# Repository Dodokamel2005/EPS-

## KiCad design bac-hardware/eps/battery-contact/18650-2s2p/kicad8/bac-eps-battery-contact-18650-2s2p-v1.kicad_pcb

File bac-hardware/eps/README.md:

# EPS v1
## Requirements
[comment]: <> (TODO turn reqs into specs on first release)
v1 of the EPS takes a low-effort approach to facilitate achieving an MVP for the whole system before starting to optimise individual subsystems. Given requirements for all parts are:

- Wide operating temperature range (industrial or automotive grade)
- Easy implementation (low BOM, good EMI/SI characteristics, solid documentation)
- Predictable availability
- Reasonable cost
- As few plastic parts as possible (low outgassing)

### PMIC
#### Minimal Requirements
- [x] Usable for both USB and solar charging
- [x] MPPT
- [x] 2S Li-Ion battery charging
- [x] Enable input pin
- [x] Fault output pin
- [x] Full complement of safety features: OVP, OCP, OTP, RVP, BBD

#### Optional Requirements
- [x] Fault output pin
- [x] Support for 1s to 4s battery packs
- [x] Support for LiFePo4 batteries
- [ ] I2C telemetry
- [ ] Adjustable charging current
- [ ] Cell balancing for 2s and 4s battery packs

### DC Buck Converter
#### Minimal Requirements
- [x] Input voltage range: 6 V to 9 V
- [x] Output voltage range: 3.3 to 5 V
- [x] 3 A per output
- [x] Enable pin
- [x] Fault output pin
- [x] Full complement of safety features: OCP, OVP, SCP, OTP, UTP, UVLO

#### Optional Requirements
- [x] 17 V input
- [x] 5 A per output
- [x] I2C telemetry
- [x] Fault output pin

### Batteries
#### Main Battery Pack (2s2p configuration)
- [x] 18650 size
- [x] Li-NiMnCoO2 or LiFePo4 chemistry
- [x] Minimum 3.5 Ah capacity
- [x] Operating temperature range: -10°C to +40°C or better
- [x] High cycle count
- [x] UL-listed

#### Coin Cell
- [x] 2032 size
- [x] LiMnO2 chemistry
- [x] Minimum 50 mAh capacity
- [x] Operating temperature range: -10°C to +40°C or better
- [x] Ideally rechargeable
- [x] UL-listed

### Solar Cells (2sNp configuration)
- [x] Size that fits a 0.25 U panel
- [x] Monocrystalline
- [x] 25% efficiency or better
- [x] Thin and light
- [x] Low-outgassing materials
- [x] Operating temperature range: -20°C to +80°C or better

## Block Diagram
```mermaid
flowchart LR

    subgraph Bus
    RAIL3V3[3.3 V Rail]
    RAIL5V[5 V Rail]
        subgraph OBC
        Microcontroller
        end
    end

    subgraph EPS
        subgraph BAT[2s2p Battery Pack]

            subgraph SER1[Series Group 1]
                BAT1[Battery 1]
                BAT2[Battery 2]
                BAT1 -- series --- BAT2
            end
            subgraph SER2[Series Group 2]
                BAT3[Battery 3]
                BAT4[Battery 4]
                BAT3 -- series --- BAT4
            end
            SER1 -- parallel --- SER2
        end
        subgraph PV[Solar Array]
            subgraph PVSTR1[0.5U PV Module 1]
                PV1[PV Cell 1a] -- series --- PV2[PV Cell 1b]
            end
            subgraph PVSTR2[0.5U PV Module 2]
                PV3[PV Cell 2a] -- series --- PV4[PV Cell 2b]
            end
            subgraph PVSTRN[0.5U PV Module N]
                PV5[PV Cell Na] -- series --- PV6[PV Cell Nb]
            end

            PVSTR1 -- parallel --- PVSTR2
            PVSTR2 -. parallel .- PVSTRN
        end
        subgraph PMIC
                CHG[Battery Charge Regulator with MPPT]
        end
        subgraph DC[DC Buck Converter]
        direction LR
            LCL2 --> DC2[Buck Converter]
            DC2 --> 5V[5 V]
            LCL1 --> DC1[Buck Converter]
            DC1 --> 3V3[3.3 V]
        end

    SENSOR1[Current, Voltage & Temp Sensor]
    SENSOR2[Current, Voltage & Temp Sensor]
    end

    PMIC ===> BAT
    PV ==> CHG
    BAT ===> DC

    PV -.- SENSOR1
    SENSOR1 -. I2C telemetry .- Microcontroller
    PMIC -.- SENSOR2
    SENSOR2 -. I2C telemetry .- Microcontroller
    DC -. I2C telemetry .- Microcontroller

    3V3 == power ==> RAIL3V3
    5V == power ==> RAIL5V

```

## Part Selection
### PMIC
- Manufacturer: Analog Devices
- Model: LTM8062 ([datasheet](https://www.analog.com/media/en/technical-documentation/data-sheets/8062fd.pdf))
- Part number: TBD
- Eval Board: DC1621A ([manual](https://www.analog.com/media/en/technical-documentation/user-guides/dc1621af.pdf))

### DC Buck Converters
- Manufacturer: Analog Devices
- Model: LTM4675 ([datasheet](https://www.analog.com/media/en/technical-documentation/data-sheets/ltm4675.pdf))
- Part number: TBD
- Eval Board: DC2053A ([manual](https://www.analog.com/media/en/technical-documentation/user-guides/DC2053AFA.PDF))

### Main Batteries
- Manufacturer: LG
- Model: MJ1 ([datasheet](https://files.batteryjunction.com/frontend/files/lg/datasheet/LG-MJ1-Datasheet.pdf))
- Part number: INR18650MJ1

### Coin Cell Battery
[comment]: <> (TODO move to OBC)
#### Option 1
- Manufacturer: Maxell
- Model: ML2032 ([datasheet](https://biz.maxell.com/en/rechargeable_batteries/ML2032_DataSheet_17e.pdf))
- Part number: ML2032 T25
#### Option 2
- Manufacturer: Maxell
- Model: CR2032HR ([datasheet](https://biz.maxell.com/en/primary_batteries/CR2032HR_DataSheet_20e.pdf))
- Part number: TBD

### Solar Cells
- Manufacturer: Anysolar
- Model: SM141K10TF ([datasheet](https://waf-e.dubudisk.com/anysolar.dubuplus.com/techsupport@anysolar.biz/O18BEt5/DubuDisk/www/Gen3/SM141K10TF%20DATA%20SHEET%20202105.pdf))
- Part number: SM141K10TF (contacts 3mm from edge) or SM141K10TFS (contacts 10mm from edge)

## Notes
This EPS is intentionally kept minimal. At the moment, there is no uC because this is supposed to be a simple device, that works as soon as the RBF and deployment switches are disengaged until one of the ICs detects an off-nominal state and shuts itself down. All telemetry and external control is going to be offloaded to a uC in the OBC via I2C.

## Disclaimer
This EPS is very much a work in progress and is in no way tested or qualified for spaceflight. Please [read the disclaimer](https://codeberg.org/buildacubesat-project/bac-hardware/src/branch/main/eps/DISCLAIMER.md) before working with this repo.

### Layout
- Pin spacing is breadboard-friendly (2.54 mm), but the spacing between groups of pins is not necessarily a multiple of 2.54 mm.
- Signal names are silkscreened on the board, top and bottom layers, where relevant.
- Panelized manufacturing files are not included.
- I recommend a stencil for assembling this board.

### PCB
- Dimensions: TBD mm * TBD mm
- Layer count: 4
- Stackup: TBD
- Thickness: 1.6 mm

## ECAD
- Software: KiCad
- Version: 8

### Future Development
- Add redundancy and watchdog circuitry
- Add dedicated load switches or MOSFETs instead of relying on the IC's internal ones for RBF and deployment switches
- Add dedicated resettable current limiters instead of relying on the DC-converter internal ones
- Add adjustable charging current
- Add full compatibility for 1s4p, 2s2p and 4s1p battery pack configurations
- Add cell balancing

### Future Investigation
- Do we need active battery heating?
- Do we need a buck-boost converter to 12 V or should we stick with bucking to 5 V and if necessary boosting to 12 V off-board? (what I believe is called a cascade configuration)

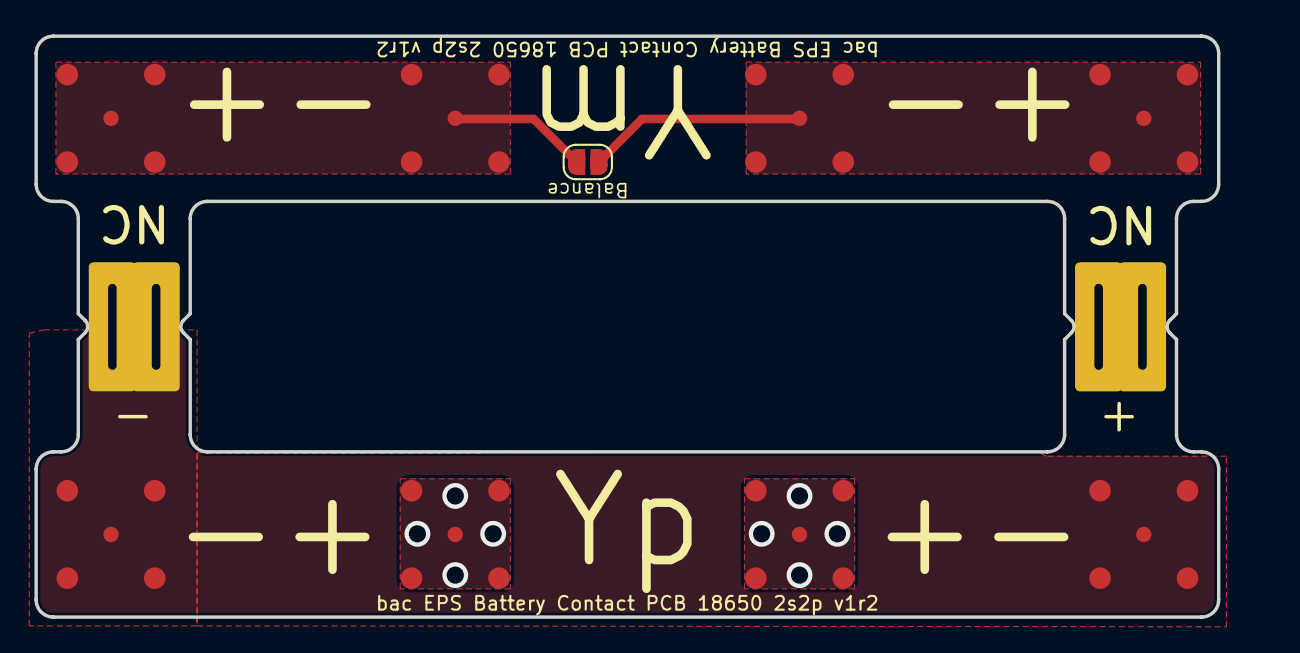
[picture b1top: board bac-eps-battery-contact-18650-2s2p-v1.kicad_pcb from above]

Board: 2 copper layers, 71.4 x 33.8 mm, 11 parts (0 on the bottom side), 4 nets.

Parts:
J1, J2: EPS_Conn; bac-eps-v1-battery-contact-pin-panelized
J5, J6, J7, J8, J9, J10, J11, J12: Contact_Dome; Snaptron-FB07
JP1: SolderJumper_2_Open; SolderJumper-2_P1.3mm_Open_RoundedPad1.0x1.5mm

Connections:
+BATT: J2.1, J6.1, J7.1
-BATT: J1.1, J5.1, J8.1
/BAL1: J9.1, J10.1, JP1.1 (A)
/BAL2: J11.1, J12.1, JP1.2 (B)

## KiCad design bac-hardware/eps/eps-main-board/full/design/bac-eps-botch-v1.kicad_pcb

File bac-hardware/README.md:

# bac-hardware

Hardware design and manufacturing files for the Build a CubeSat project. Includes ECAD files, BOMs, gerber files, notes and other relevant artifacts.

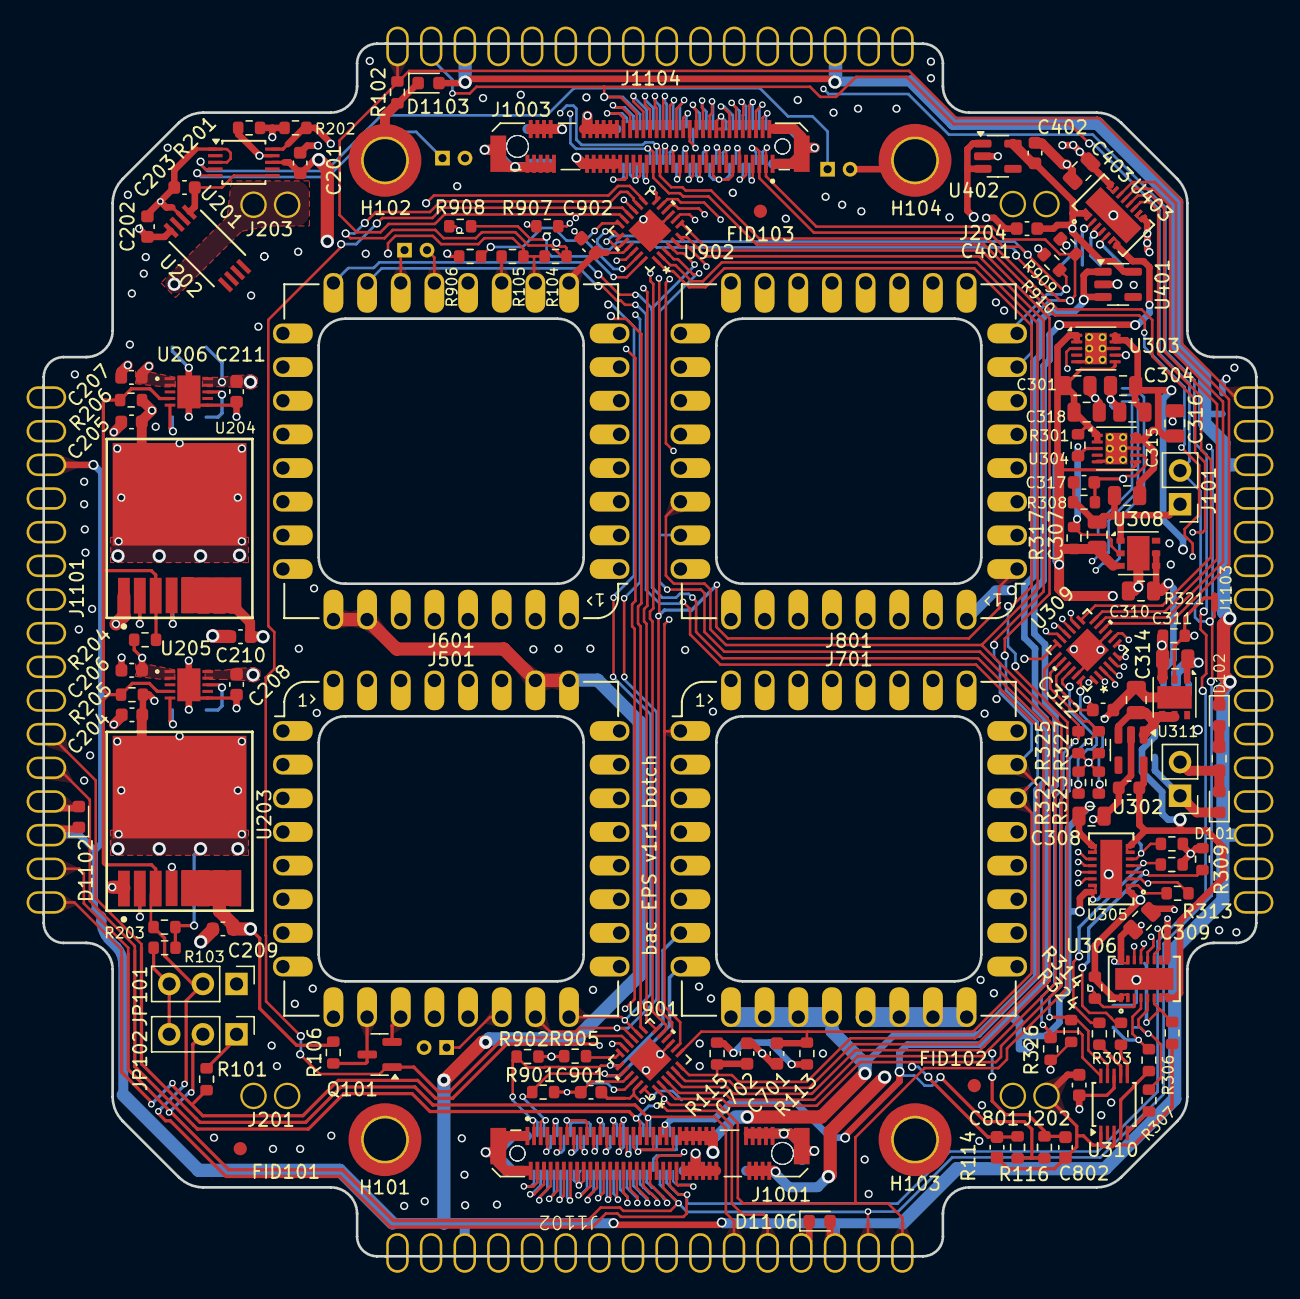
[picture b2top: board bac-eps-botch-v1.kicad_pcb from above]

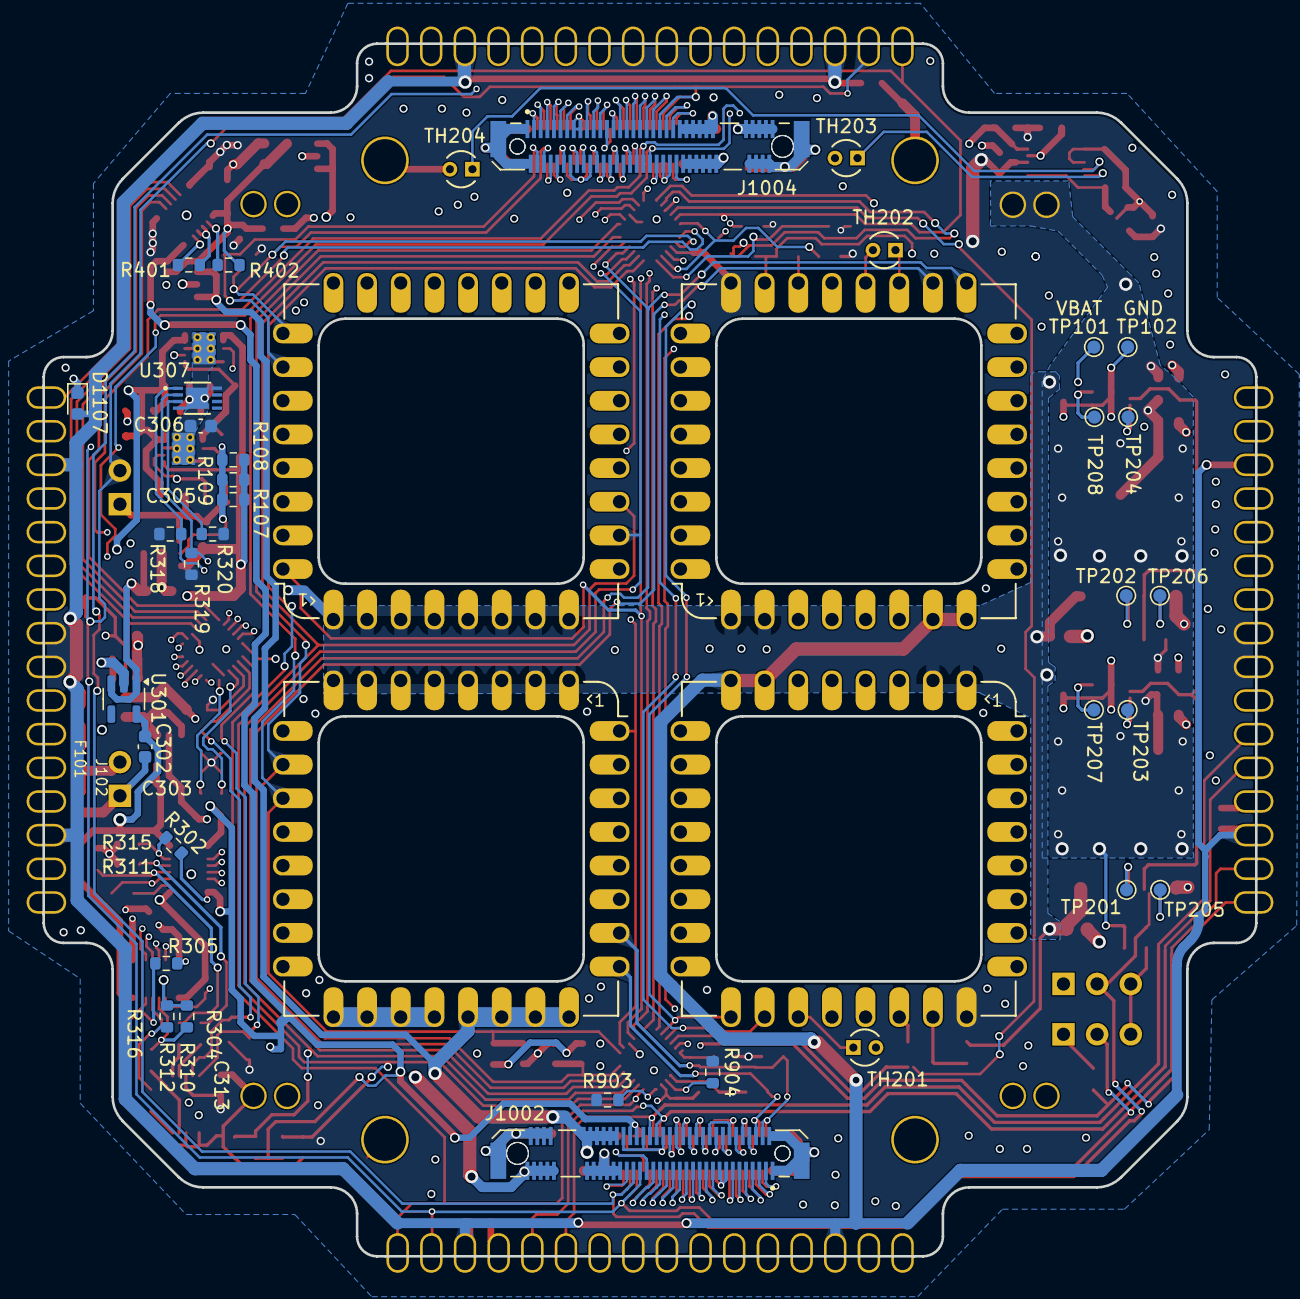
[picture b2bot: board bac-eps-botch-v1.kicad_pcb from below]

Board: 4 copper layers, 91.5 x 91.5 mm, 174 parts (36 on the bottom side), 157 nets.

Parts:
C201, C202, C203, C204, C205, C206, C207, C208, C209, C210, C211, C302, C303, C306, C312, C313, C317, C401, C402, C701, C702, C801, C802, C901, C902: 1u; C_0603_1608Metric
C301, C304, C305, C307, C308, C309, C310, C311, C314, C315, C316, C318, C403: 10u; C_0805_2012Metric
D101, D1102, D1103, D1106, D1107: PGB1010603MR; D_0603_1608Metric
D102: NSR20F40NXT5G; D_0603_1608Metric
F101: 0438006.WRA; R_0603_1608Metric_Pad0.98x0.95mm_HandSolder
FID101, FID102, FID103: Fiducial; Fiducial_1mm_Mask2mm
H101, H102, H103, H104: MountingHole_Pad; MountingHole_3.2mm_M3_ISO14580_Pad_TopOnly
J101, J102: Conn_01x02; PinHeader_1x02_P2.54mm_Vertical
J201, J202, J203, J204: Conn_01x02_Pin; Mill-Max-0630-0-15-15-30-27-10-0-PN-1x02-P2.54
J501, J601, J701, J801: bac-eps-v1-module-landing-pad
J1001, J1002: AMP MDT350M01001VT; AMP-MDT350M01001VT
J1003, J1004: BMP MDT350M01001VT; AMP-MDT350M01001VT
J1101, J1102, J1103, J1104: Panel Connector 1x16; Mill-Max-0630-0-15-15-30-27-10-0-SE-1x16-P2.54
JP101, JP102: Jumper_3_Open; PinHeader_1x03_P2.54mm_Vertical
NT101, NT301, NT302, NT401, NT402: NetTie_2; NetTie-2_SMD_Pad0.5mm
NT303, NT304: NetTie_3_Tee; NetTie-3_SMD_Pad0.5mm
Q101: DMN62D0U-7; SOT-23
R101, R102, R105, R107, R108, R109, R113, R114, R115, R116, R203, R204, R205, R206, R301, R302, R303, R304, R306, R307, R313, R314, R315, R316, R317, R321, R401, R402: 100k; R_0603_1608Metric
R103, R201, R202, R318, R319, R320, R322, R323, R324, R325, R326, R327, R901, R902, R903, R904, R905, R906, R907, R908, R909, R910: 10k; R_0603_1608Metric
R104, R106, R305: 47k; R_0603_1608Metric
R308: 16k; R_0603_1608Metric
R309, R310, R311, R312: 2k; R_0603_1608Metric
TH201, TH202, TH203, TH204: NTC 10k; Cantherm-MF52A1103F3380
TP101, TP102, TP201, TP202, TP203, TP204, TP205, TP206, TP207, TP208: TestPoint; TestPoint_Pad_D1.0mm
U201, U310: ADS1015IRUGR; TSSOP-10_3x3mm_P0.5mm
U202: ACS37612LLUATR-015B5; AL-ACS37612LLUATR-010B3
U203, U204: BTS50005-1LUA; INF-BTS50005-1LUA
U205, U206: SIPQ32434BDN-T1E3; VIS-SIPQ32434BDN-T1E3
U301, U302, U401, U402: MAX40200AUK; SOT-23-5
U303, U304: LT3045MPDD; ADI-LT3045MPDD
U305, U306, U403: LTC4415EDHC; ADI-LTC4415EDHC
U307: PCT2075TP; NXP-PCT2075TP,147
U308, U311: LDO40LPU33RY
U309, U901, U902: TCAL9539RTWR; TI-TCAL9539RTWR

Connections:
+3V3_OR: C201.2, C202.2, C306.2, C312.2, C313.2, C403.1, C901.2, C902.2, J501.24, J601.24, J1101.8, J1101.9, J1102.8, J1102.9, J1103.8, J1103.9, J1104.8, J1104.9, NT401.1, NT402.2, R201.1, R202.1, R318.1, R319.1, R320.1, R322.1, R323.1, R324.1, R325.1, R326.1, R327.1, R901.1, R902.1, R903.1, R904.1, R905.1, R906.1, R907.1, R908.1, R909.1, R910.1, U201.8 (VDD), U202.4 (VCC), U307.8 (VCC), U309.21 (VCC), U310.8 (VDD), U901.21 (VCC), U902.21 (VCC)
+12V: D101.2 (A2), F101.1, J102.2
+BATT: C204.2, C205.2, C206.2, C207.2, J203.1, J203.2, R103.1, R203.2, R204.2, R205.2, R206.2, U203.EPAD (VS), U204.EPAD (VS), U205.1 (VIN), U205.2 (VIN), U206.1 (VIN), U206.2 (VIN)
/+3V3_AUX/EN_SYS: J1001.41, J1001.43, J1002.42, J1002.44, J1003.41, J1003.43, J1004.42, J1004.44, NT303.3, R113.1, R114.1, R115.1, R116.1, U403.7 (IN2), U403.8 (IN2)
/+3V3_MAIN_A: J701.21, J701.22, J701.23, J701.24, J1001.47, J1001.49, J1001.51, J1001.53, J1001.55, J1001.57, J1002.48, J1002.50, J1002.52, J1002.54, J1002.56, J1002.58, U401.1 (VDD), U401.3 (EN)
/+3V3_MAIN_B: J801.21, J801.22, J801.23, J801.24, J1003.47, J1003.49, J1003.51, J1003.53, J1003.55, J1003.57, J1004.48, J1004.50, J1004.52, J1004.54, J1004.56, J1004.58, U402.1 (VDD), U402.3 (EN)
/+5V_MAIN_A: J701.17, J701.18, J701.19, J701.20, J1001.68, J1001.70, J1001.72, J1001.74, J1002.67, J1002.69, J1002.71, J1002.73, J1002.75
/+5V_MAIN_B: J801.17, J801.18, J801.19, J801.20, J1003.68, J1003.70, J1003.72, J1003.74, J1004.67, J1004.69, J1004.71, J1004.73, J1004.75
/BAT_NTC_A: J501.19, TH201.1
/BAT_NTC_B: J601.19, TH202.1
/BCHG_A_OVR: Q101.1 (G), U901.16, U902.16
/BCHG_A_~CHRG: J501.18, U901.15, U902.15
/BCHG_A_~FAULT: J501.17, R104.2, U901.14, U902.14
/BCHG_B_OVR: J601.23, R104.1, R105.2, U901.13, U902.13
/BCHG_B_~CHRG: J601.18, U901.5, U902.5
/BCHG_B_~FAULT: J601.17, U901.4, U902.4
/Battery Charger Module A/EN: J501.23, Q101.3 (D), R106.1
/Battery Pack/IMON: C203.2, U201.6 (AIN2), U202.1 (VOUT)
/Battery Pack/NTC_3: TH203.1, U201.5 (AIN1)
/Battery Pack/NTC_4: TH204.1, U201.4 (AIN0)
/DEPLOY_1: J1001.44, J1002.43, J1003.44, J1004.43, JP101.2 (C), R203.1, R204.1, R205.1, R206.1, U203.3 (EN), U204.3 (EN), U205.4 (EN/UVLO), U206.4 (EN/UVLO)
/DEPLOY_2/RBF: J101.2, J1001.42, J1002.41, J1003.42, J1004.41, J1101.2, J1102.2, J1103.2, J1104.2, JP102.2 (C), NT101.1
/EN_LDO: NT101.2, R107.1, R108.1, R109.1, R301.2, R317.1, R321.1, U303.3 (EN/UV), U304.3 (EN/UV), U308.2 (EN), U311.2 (EN)
/EPS Power Path/OR_OUT_1: NT401.2, U403.15 (OUT1), U403.16 (OUT1)
/EPS Power Path/OR_OUT_2: NT402.1, U403.9 (OUT2), U403.10 (OUT2)
/EPS_OVR_AUX: R401.2, U403.6 (~EN2), U901.12, U902.12
/EPS_OVR_MAIN: R402.1, U403.3 (EN1), U901.11, U902.11
/I2C Expanders/I2C_INT_A: R904.2, U901.22 (*INT)
/I2C Expanders/I2C_INT_B: R907.2, U902.22 (*INT)
/I2C Expanders/I2C_RST_A: R903.2, U901.24 (*RESET)
/I2C Expanders/I2C_RST_B: R908.2, U902.24 (*RESET)
/LDOs/+3V3_LDO_1: NT304.3, R313.2, R314.2, U305.1 (IN1), U305.2 (IN1), U306.1 (IN1), U306.2 (IN1)
/LDOs/+3V3_LDO_1A: C304.1, C315.1, NT304.1, U303.9 (OUTS), U303.10 (OUT)
/LDOs/+3V3_LDO_1B: C305.1, C316.1, NT304.2, U304.9 (OUTS), U304.10 (OUT)
/LDOs/+3V3_LDO_2: C310.1, U301.1 (VDD), U301.3 (EN), U308.4 (VOUT), U308.5 (SENSE)
/LDOs/+3V3_LDO_3: C314.1, U302.1 (VDD), U302.3 (EN), U311.4 (VOUT), U311.5 (SENSE)
/LDOs/I2C_INT: R322.2, U309.22 (*INT)
/LDOs/I2C_RST: R323.2, U309.24 (*RESET)
/LDOs/OR_A_EN_1: R313.1, U305.3 (EN1), U309.15
/LDOs/OR_A_IMON_1: R303.1, U310.6 (AIN2)
/LDOs/OR_A_IMON_2: R304.1, U310.7 (AIN3)
/LDOs/OR_A_OUT_1: NT302.2, R302.1, U305.15 (OUT1), U305.16 (OUT1)
/LDOs/OR_A_OUT_2: C308.1, NT302.1, NT303.2, U305.9 (OUT2), U305.10 (OUT2)
/LDOs/OR_A_STAT_1: U305.14 (~STAT1), U309.4
/LDOs/OR_A_STAT_2: U305.12 (~WARN2), U309.2
/LDOs/OR_A_WARN_1: U305.13 (~WARN1), U309.3
/LDOs/OR_A_WARN_2: U305.11 (~STAT2), U309.1
/LDOs/OR_A_~EN_2: R302.2, R315.2, U305.6 (~EN2), U309.14
/LDOs/OR_B_EN_1: R314.1, U306.3 (EN1), U309.17
/LDOs/OR_B_IMON_1: R306.1, U310.4 (AIN0)
/LDOs/OR_B_IMON_2: R307.1, U310.5 (AIN1)
/LDOs/OR_B_OUT_1: NT301.2, R305.1, U306.15 (OUT1), U306.16 (OUT1)
/LDOs/OR_B_OUT_2: C309.1, NT301.1, NT303.1, U306.9 (OUT2), U306.10 (OUT2)
/LDOs/OR_B_STAT_1: U306.14 (~STAT1), U309.8
/LDOs/OR_B_STAT_2: U306.12 (~WARN2), U309.6
/LDOs/OR_B_WARN_1: U306.13 (~WARN1), U309.7
/LDOs/OR_B_WARN_2: U306.11 (~STAT2), U309.5
/LDOs/OR_B_~EN_2: R305.2, R316.2, U306.6 (~EN2), U309.16
/MAMOD_A_CAN_1_N: J1001.17, J1002.18
/MAMOD_A_CAN_1_P: J1001.15, J1002.16
/MAMOD_A_I2C_1_SCL: J701.26, J1001.3, J1002.4, R319.2, R325.2, R326.2, R902.2, U307.2 (SCL), U309.19 (SCL), U310.10 (SCL), U901.19 (SCL)
/MAMOD_A_I2C_1_SDA: J701.25, J1001.5, J1002.6, R318.2, R324.2, R327.2, R901.2, U307.1 (SDA), U309.20 (SDA), U310.9 (SDA), U901.20 (SDA)
/MAMOD_A_I2C_2_SCL: J1001.35, J1002.36, J1101.5, J1102.5
/MAMOD_A_I2C_2_SDA: J1001.37, J1002.38, J1101.6, J1102.6
/MAMOD_B_CAN_1_N: J1003.17, J1004.18
/MAMOD_B_CAN_1_P: J1003.15, J1004.16
/MAMOD_B_I2C_1_SCL: J801.26, J1003.3, J1004.4, R202.2, R909.2, U201.10 (SCL), U902.19 (SCL)
/MAMOD_B_I2C_1_SDA: J801.25, J1003.5, J1004.6, R201.2, R910.2, U201.9 (SDA), U902.20 (SDA)
/MAMOD_B_I2C_2_SCL: J1003.35, J1004.36, J1103.5, J1104.5
/MAMOD_B_I2C_2_SDA: J1003.37, J1004.38, J1103.6, J1104.6
/MacroMod Connectors/3A: J1001.4, J1002.3
/MacroMod Connectors/3B: J1003.4, J1004.3
/MacroMod Connectors/5A: J1001.6, J1002.5
/MacroMod Connectors/5B: J1003.6, J1004.5
/MacroMod Connectors/7A: J1001.8, J1002.7
/MacroMod Connectors/7B: J1003.8, J1004.7
/MacroMod Connectors/9A: J1001.10, J1002.9
/MacroMod Connectors/9B: J1003.10, J1004.9
/MacroMod Connectors/10A: J1001.9, J1002.10
/MacroMod Connectors/10B: J1003.9, J1004.10
/MacroMod Connectors/11A: J1001.12, J1002.11
/MacroMod Connectors/11B: J1003.12, J1004.11
/MacroMod Connectors/12A: J1001.11, J1002.12
/MacroMod Connectors/12B: J1003.11, J1004.12
/MacroMod Connectors/13A: J1001.14, J1002.13
/MacroMod Connectors/13B: J1003.14, J1004.13
/MacroMod Connectors/19A: J1001.20, J1002.19
/MacroMod Connectors/19B: J1003.20, J1004.19
/MacroMod Connectors/21A: J1001.22, J1002.21
/MacroMod Connectors/21B: J1003.22, J1004.21
/MacroMod Connectors/22A: J1001.21, J1002.22
/MacroMod Connectors/22B: J1003.21, J1004.22
/MacroMod Connectors/23A: J1001.24, J1002.23
/MacroMod Connectors/23B: J1003.24, J1004.23
/MacroMod Connectors/24A: J1001.23, J1002.24
/MacroMod Connectors/24B: J1003.23, J1004.24
/MacroMod Connectors/25A: J1001.26, J1002.25
/MacroMod Connectors/25B: J1003.26, J1004.25
/MacroMod Connectors/26A: J1001.25, J1002.26
/MacroMod Connectors/26B: J1003.25, J1004.26
/MacroMod Connectors/27A: J1001.28, J1002.27
/MacroMod Connectors/27B: J1003.28, J1004.27
/MacroMod Connectors/28A: J1001.27, J1002.28
/MacroMod Connectors/28B: J1003.27, J1004.28
/MacroMod Connectors/29A: J1001.30, J1002.29
/MacroMod Connectors/29B: J1003.30, J1004.29
/MacroMod Connectors/30A: J1001.29, J1002.30
/MacroMod Connectors/30B: J1003.29, J1004.30
/MacroMod Connectors/31A: J1001.32, J1002.31
/MacroMod Connectors/31B: J1003.32, J1004.31
/MacroMod Connectors/32A: J1001.31, J1002.32
/MacroMod Connectors/32B: J1003.31, J1004.32
/MacroMod Connectors/33A: J1001.34, J1002.33
/MacroMod Connectors/33B: J1003.34, J1004.33
/MacroMod Connectors/35A: J1001.36, J1002.35
/MacroMod Connectors/35B: J1003.36, J1004.35
/MacroMod Connectors/37A: J1001.38, J1002.37
/MacroMod Connectors/37B: J1003.38, J1004.37
/MacroMod Connectors/39A: J1001.40, J1002.39
/MacroMod Connectors/39B: J1003.40, J1004.39
/MacroMod Connectors/45A: J1001.46, J1002.45
/MacroMod Connectors/45B: J1003.46, J1004.45
/PANEL_m_EN: J1101.1, J1102.1, R101.2, U901.1, U902.1
/PANEL_p_EN: J1103.1, J1104.1, R102.2, U901.17, U902.17
/REG_A_OVR_1: C702.2, J701.10, R115.2, U901.6, U902.6
/REG_A_OVR_2: C701.2, J701.11, R113.2, U901.7, U902.7
/REG_A_~FAULT: J701.32, U901.8, U902.8
/REG_B_OVR_1: C802.2, J801.10, R116.2, U901.3, U902.3
/REG_B_OVR_2: C801.2, J801.11, R114.2, U901.2, U902.2
/REG_B_~FAULT: J801.32, U901.10, U902.10
/VBAT: C208.2, C209.2, C210.2, C211.2, C301.1, C307.1, C311.1, C318.1, J501.1, J501.2, J601.1, J601.2, J701.1, J701.2, J701.3, J701.4, J701.5, J701.6, J701.7, J701.8, J801.1, J801.2, J801.3, J801.4, J801.5, J801.6, J801.7, J801.8, R106.2, R107.2, R108.2, R109.2, R301.1, R317.2, R321.2, TP101.1, U203.5 (OUT), U203.6 (OUT), U203.7 (OUT), U203.8 (OUT), U204.5 (OUT), U204.6 (OUT), U204.7 (OUT), U204.8 (OUT), U205.9 (VOUT), U205.10 (VOUT), U206.9 (VOUT), U206.10 (VOUT), U303.1 (IN), U303.2 (IN), U303.6 (PGFB), U304.1 (IN), U304.2 (IN), U304.6 (PGFB), U308.3 (VIN), U311.3 (VIN)
/VPV: D102.1 (K), D1102.1 (A1), D1103.2 (A2), D1106.2 (A2), D1107.2 (A2), J501.7, J501.8, J601.7, J601.8, J1101.3, J1101.14, J1102.3, J1102.14, J1103.3, J1103.14, J1104.3, J1104.14
GND: C201.1, C202.1, C203.1, C204.1, C205.1, C206.1, C207.1, C208.1, C209.1, C210.1, C211.1, C301.2, C302.1, C303.1, C304.2, C305.2, C306.1, C307.2, C308.2, C309.2, C310.2, C311.2, C312.1, C313.1, C314.2, C315.2, C316.2, C317.1, C318.2, C401.1, C402.1, C403.2, C701.1, C702.1, C801.1, C802.1, C901.1, C902.1, D101.1 (A1), D1102.2 (A2), D1103.1 (A1), D1106.1 (A1), D1107.1 (A1), H101.1, H102.1, H103.1, H104.1, J101.1, J102.1, J201.1, J201.2, J202.1, J202.2, J204.1, J204.2, J501.3, J501.4, J501.5, J501.6, J501.9, J501.10, J501.11, J501.12, J501.13, J501.14, J501.15, J501.16, J501.20, J501.21, J501.22, J501.25, J501.26, J501.27, J501.28, J501.29, J501.30, J501.31, J501.32, J601.3, J601.4, J601.5, J601.6, J601.9, J601.10, J601.11, J601.12, J601.13, J601.14, J601.15, J601.16, J601.20, J601.21, J601.22, J601.25, J601.26, J601.27, J601.28, J601.29, J601.30, J601.31, J601.32, J701.12, J701.13, J701.14, J701.15, J701.16, J701.27, J701.28, J701.29, J801.12, J801.13, J801.14, J801.15, J801.16, J801.27, J801.28, J801.29, J1001.1, J1001.2, J1001.7, J1001.13, J1001.16, J1001.18, J1001.19, J1001.33, J1001.39, J1001.45, J1001.48, J1001.50, J1001.52, J1001.54, J1001.56, J1001.58, J1001.67, J1001.69, J1001.71, J1001.73, J1001.75, J1001.S1 (SHIELD), J1001.S2 (SHIELD__1), J1002.1, J1002.2, J1002.8, J1002.14, J1002.15, J1002.17, J1002.20, J1002.34, J1002.40, J1002.46, J1002.47, J1002.49, J1002.51, J1002.53, J1002.55, J1002.57, J1002.68, J1002.70, J1002.72, J1002.74, J1002.S1 (SHIELD), J1002.S2 (SHIELD__1), J1003.1, J1003.2, J1003.7, J1003.13, J1003.16, J1003.18, J1003.19, J1003.33, J1003.39, J1003.45, J1003.48, J1003.50, J1003.52, J1003.54, J1003.56, J1003.58, J1003.67, J1003.69, J1003.71, J1003.73, J1003.75, J1003.S1 (SHIELD), J1003.S2 (SHIELD__1), J1004.1, J1004.2, J1004.8, J1004.14, J1004.15, J1004.17, J1004.20, J1004.34, J1004.40, J1004.46, J1004.47, J1004.49, J1004.51, J1004.53, J1004.55, J1004.57, J1004.68, J1004.70, J1004.72, J1004.74, J1004.S1 (SHIELD), J1004.S2 (SHIELD__1), J1101.4, J1101.7, J1101.10, J1101.13, J1102.4, J1102.7, J1102.10, J1102.13, J1103.4, J1103.7, J1103.10, J1103.13, J1104.4, J1104.7, J1104.10, J1104.13, JP101.1 (A), JP102.1 (A), Q101.2 (S), R101.1, R102.1, R105.1, R308.2, R309.1, R310.1, R311.1, R312.1, R315.1, R316.1, R401.1, TH201.2, TH202.2, TH203.2, TH204.2, TP102.1, U201.1 (ADDR), U201.3 (GND), U202.2 (GND), U203.1 (GND), U204.1 (GND), U205.6 (GND), U205.11 (GND), U206.6 (GND), U206.11 (GND), U301.2 (GND), U302.2 (GND), U303.5 (ILIM), U303.8 (GND), U303.11 (EPAD), U304.5 (ILIM), U304.8 (GND), U304.11 (EPAD), U305.17 (GND), U306.17 (GND), U307.4 (GND), U307.9 (EPAD), U308.1 (GND), U308.7 (EPAD), U309.9 (GND), U309.18 (A0), U309.23 (A1), U309.25 (EPAD), U310.1 (ADDR), U310.3 (GND), U311.1 (GND), U311.7 (EPAD), U401.2 (GND), U402.2 (GND), U403.4 (CLIM1), U403.5 (CLIM2), U403.17 (GND), U901.9 (GND), U901.23 (A1), U901.25 (EPAD), U902.9 (GND), U902.25 (EPAD)
unnamed: D102.2 (A), F101.2
unnamed: JP101.3 (B), JP102.3 (B), R103.2
unnamed: TP205.1, U203.2 (DIAG)
unnamed: TP201.1, U203.4 (DIAG_EN)
unnamed: TP206.1, U204.2 (DIAG)
unnamed: TP202.1, U204.4 (DIAG_EN)
unnamed: TP203.1, U205.5 (ILIM/IMON)
unnamed: TP207.1, U205.8 (PGD)
unnamed: TP204.1, U206.5 (ILIM/IMON)
unnamed: TP208.1, U206.8 (PGD)
unnamed: C302.2, C303.2, U301.5 (OUT), U302.5 (OUT), U305.7 (IN2), U305.8 (IN2), U306.7 (IN2), U306.8 (IN2)
unnamed: C317.2, R308.1, U303.7 (SET), U304.7 (SET)
unnamed: R303.2, R309.2, U305.4 (CLIM1)
unnamed: R304.2, R311.2, U305.5 (CLIM2)
unnamed: R306.2, R310.2, U306.4 (CLIM1)
unnamed: R307.2, R312.2, U306.5 (CLIM2)
unnamed: R320.2, U307.3 (OS)
unnamed: C401.2, C402.2, R402.2, U401.5 (OUT), U402.5 (OUT), U403.1 (IN1), U403.2 (IN1)
unnamed: R905.2, U901.18 (A0)
unnamed: R906.2, U902.18 (A0), U902.23 (A1)
OR_C_STAT_1: U309.10, U403.14 (~STAT1)
OR_C_STAT_2: U309.12, U403.12 (~WARN2)
OR_C_WARN_1: U309.11, U403.13 (~WARN1)
OR_C_WARN_2: U309.13, U403.11 (~STAT2)

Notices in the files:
bac-hardware/eps/battery-charger-module/ltm8062-charger-module/kicad8/bac-eps-ltm8062-charger-module-v1.kicad_pcb:
CC BY-SA 4.0
